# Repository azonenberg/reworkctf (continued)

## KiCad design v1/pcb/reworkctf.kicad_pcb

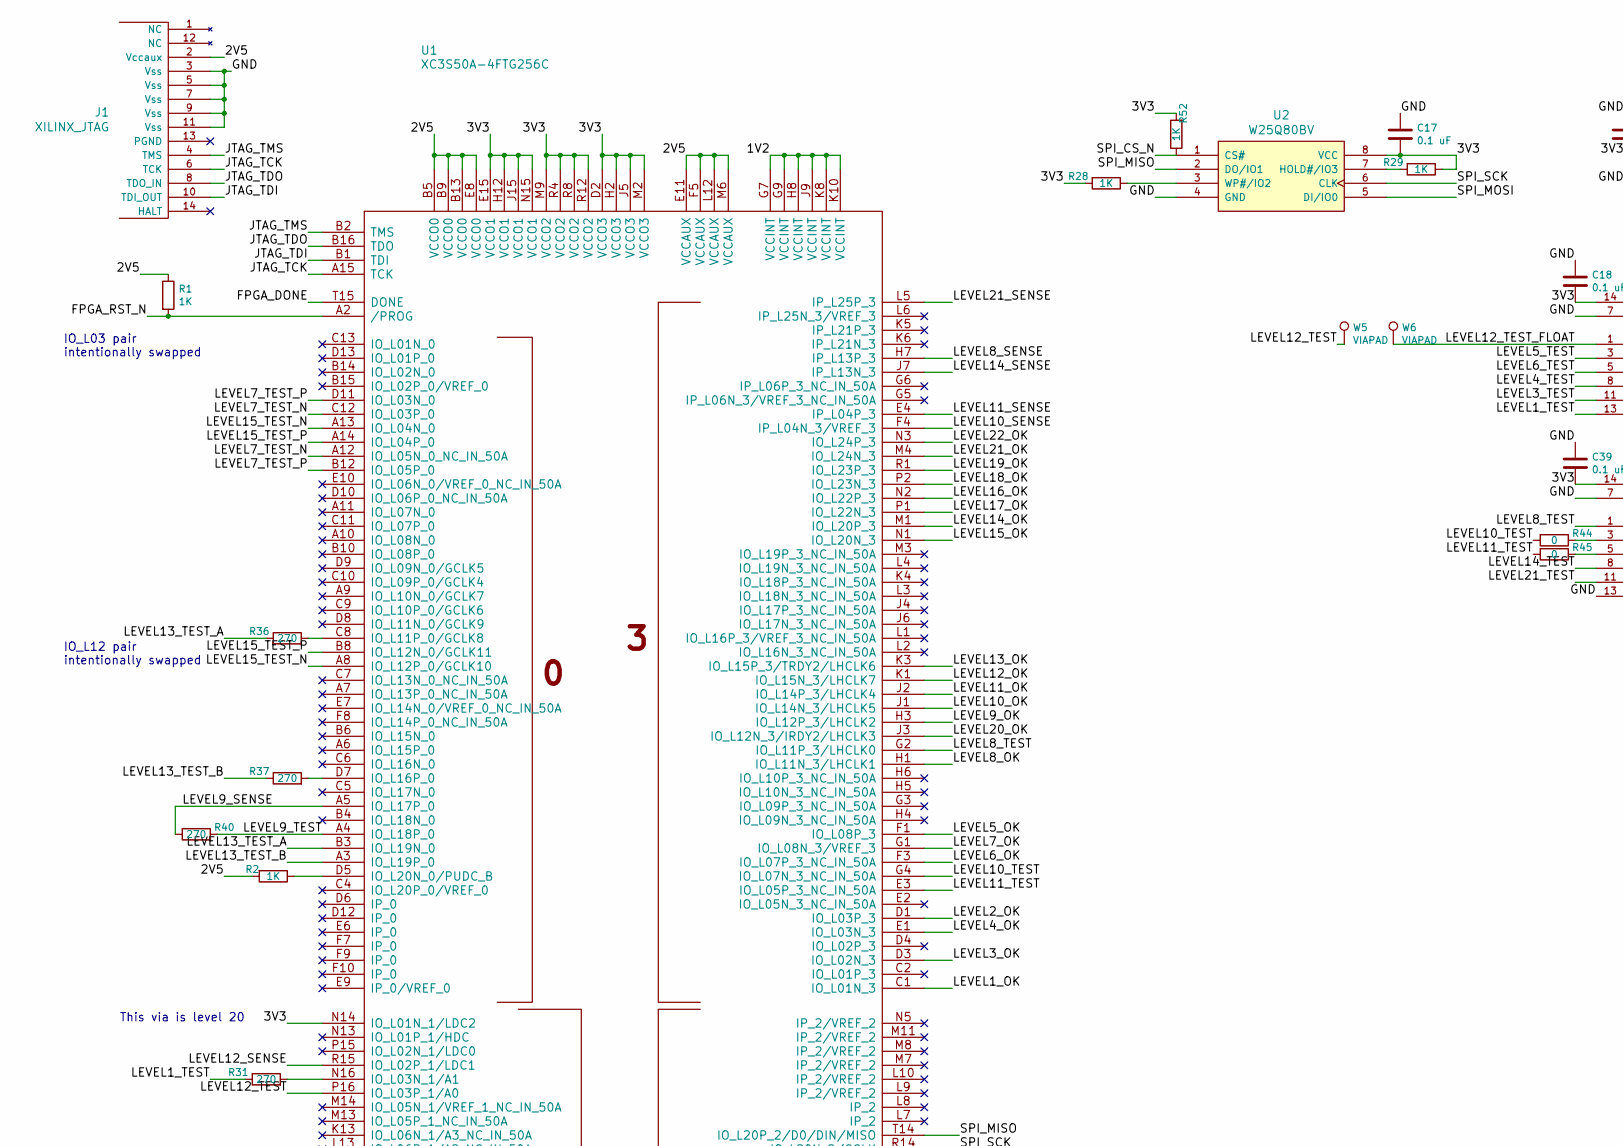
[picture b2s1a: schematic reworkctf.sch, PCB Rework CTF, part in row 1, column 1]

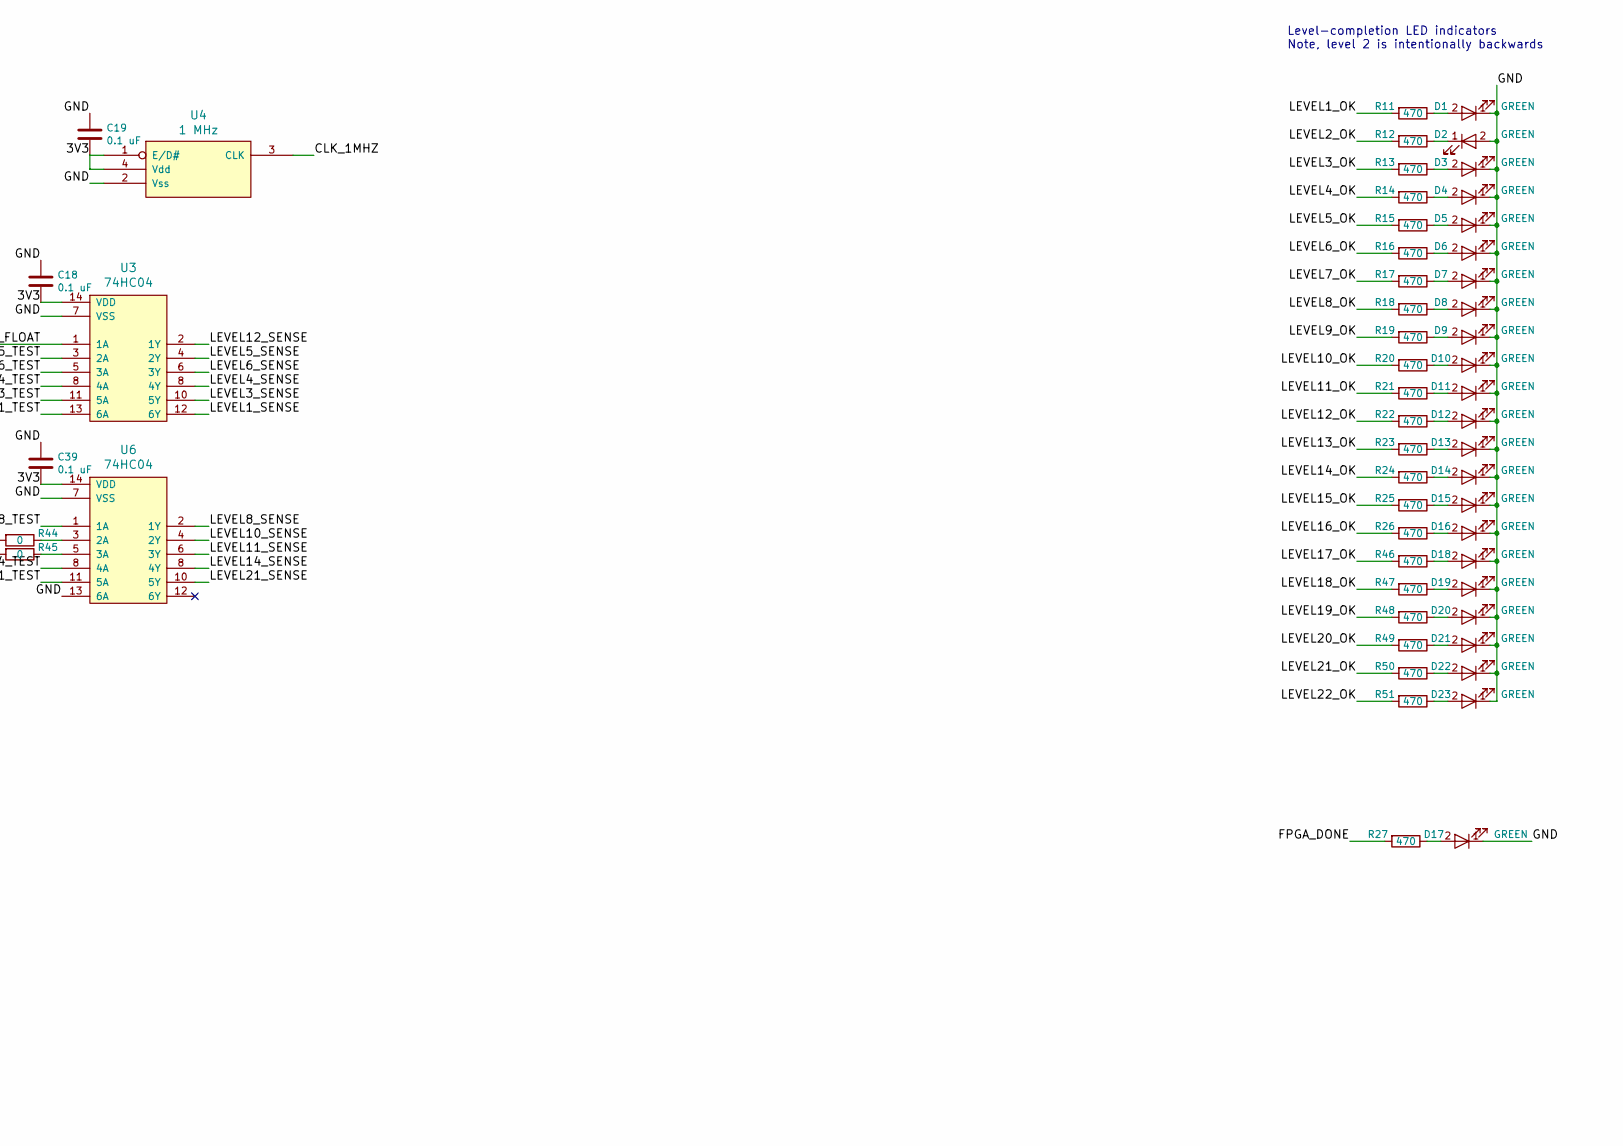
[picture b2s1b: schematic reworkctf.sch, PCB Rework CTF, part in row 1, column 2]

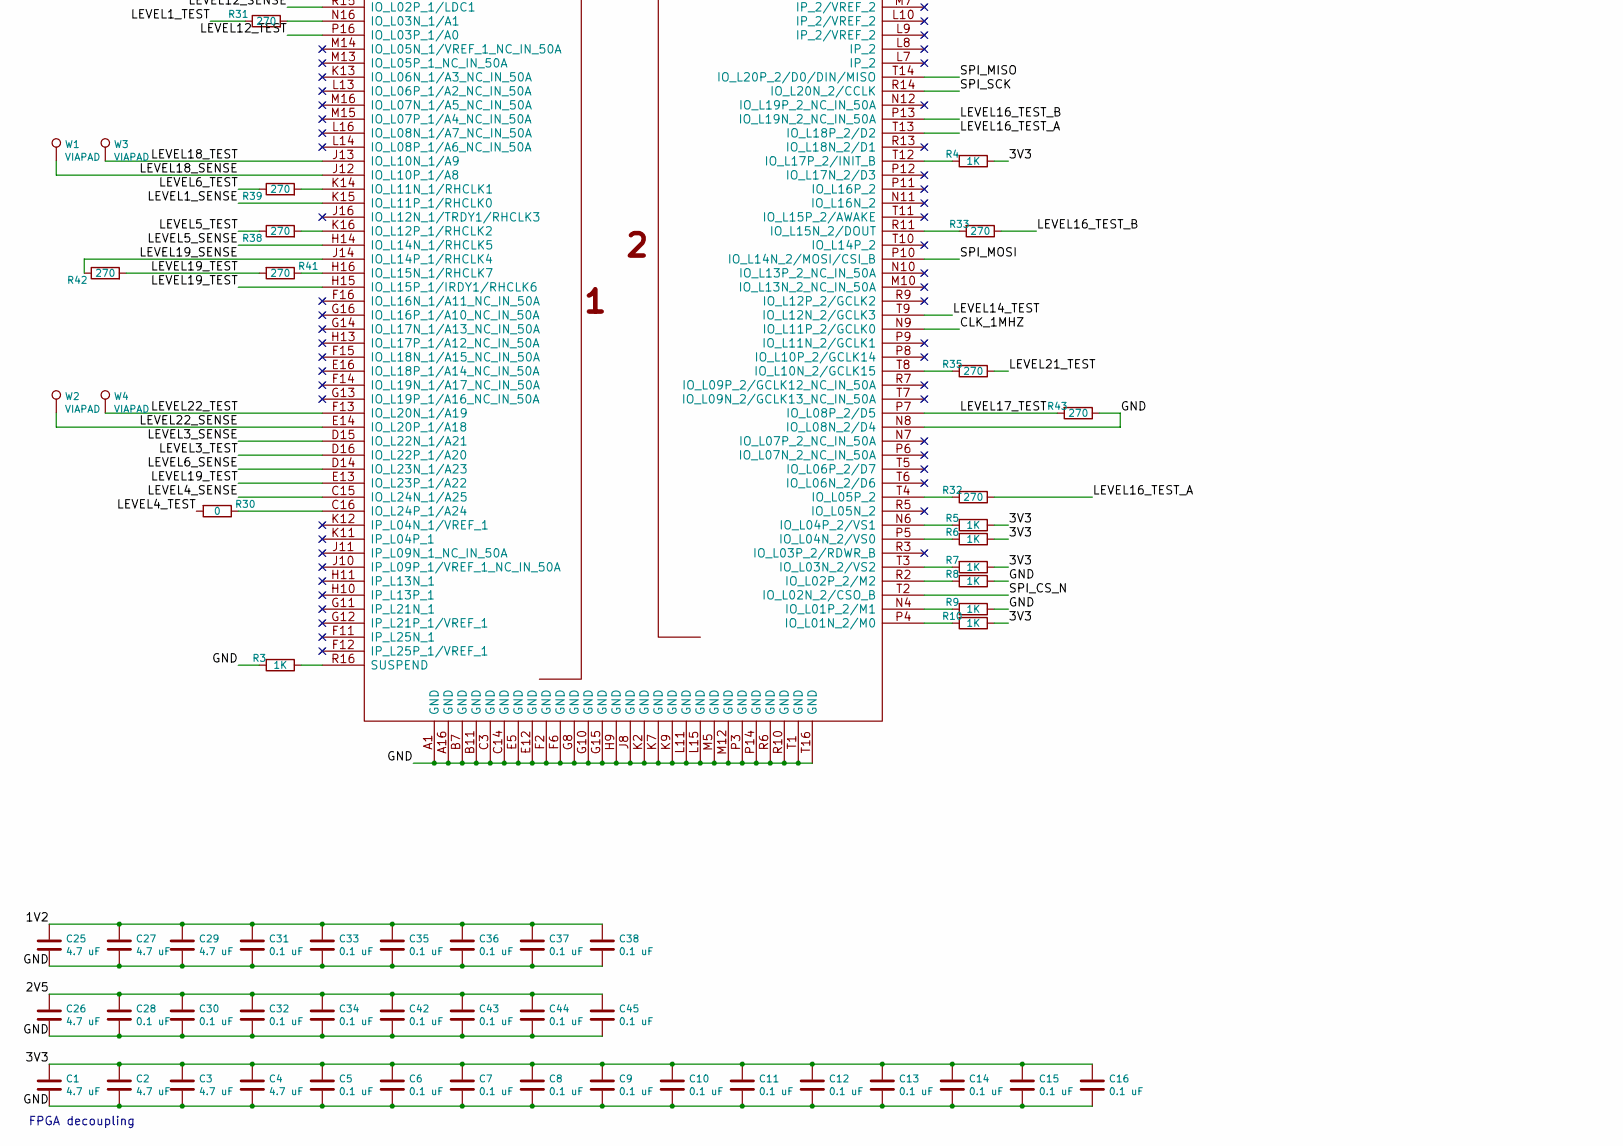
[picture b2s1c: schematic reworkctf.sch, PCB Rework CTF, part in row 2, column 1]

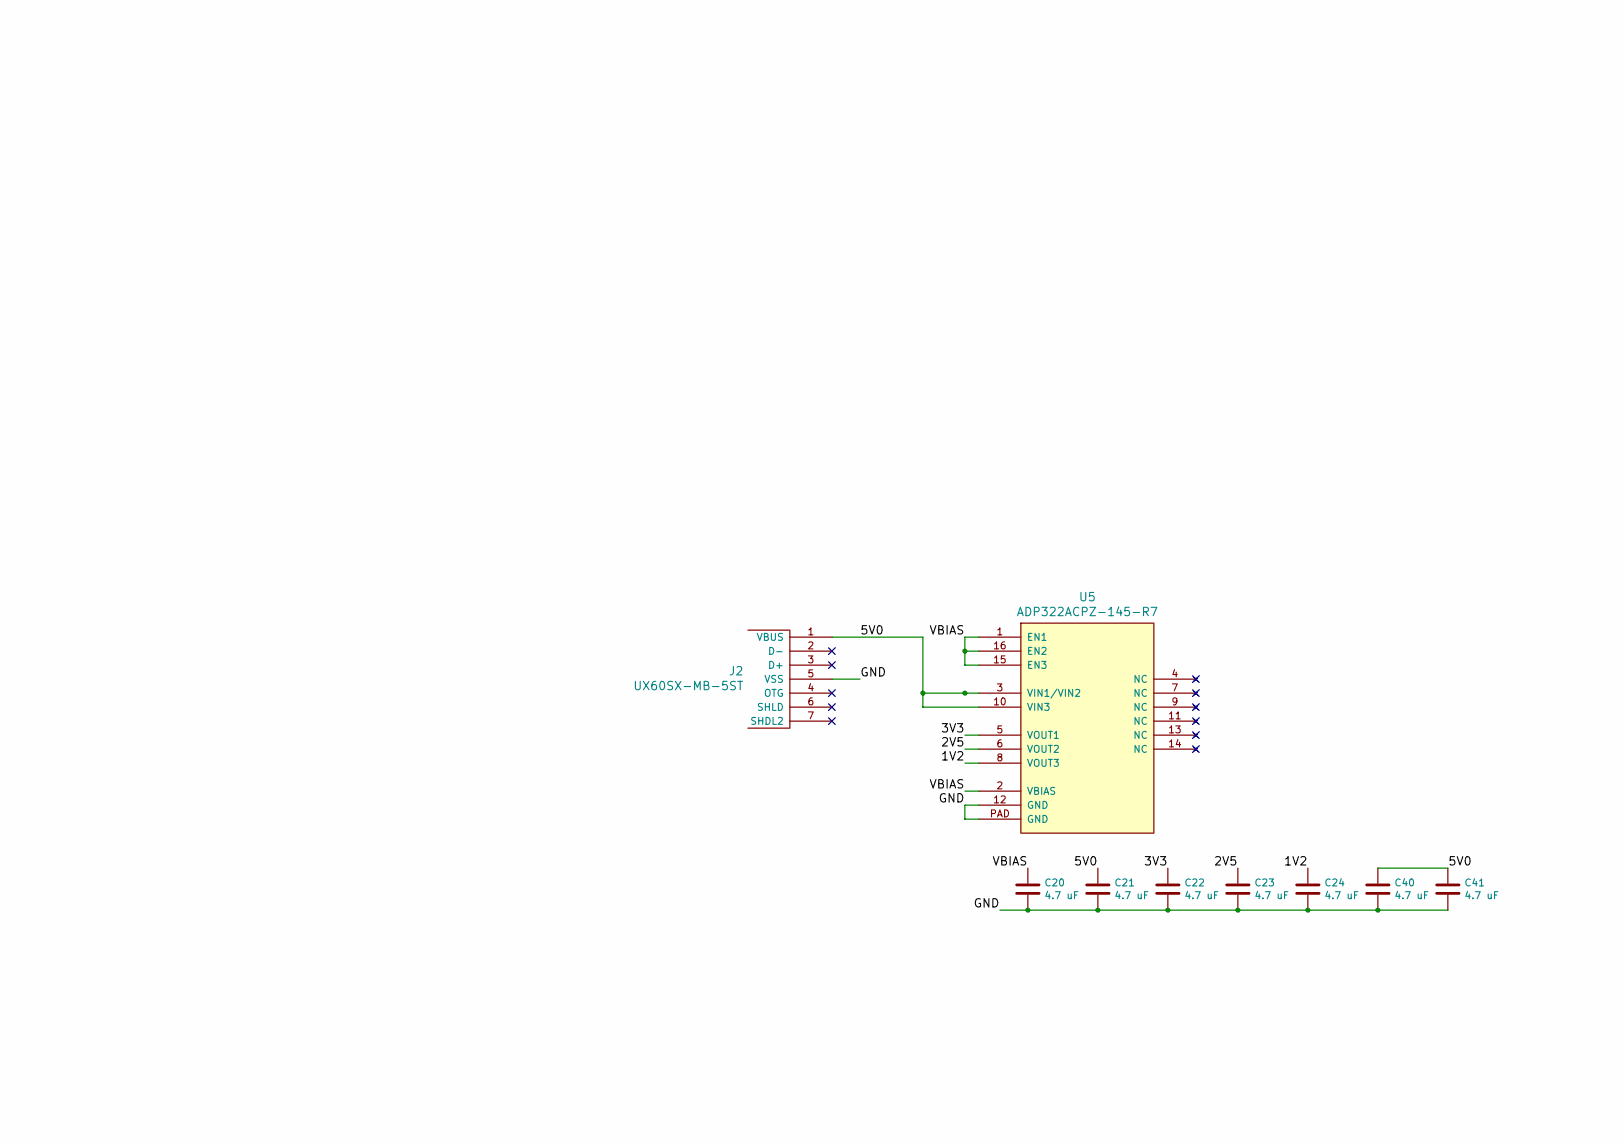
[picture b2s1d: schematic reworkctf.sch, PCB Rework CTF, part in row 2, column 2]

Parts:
C1, C2, C3, C4, C20, C21, C22, C23, C24, C25, C26, C27, C29, C40, C41: 4.7 uF; EIA_0603_CAP_NOSILK
C5, C6, C7, C8, C9, C10, C11, C12, C13, C14, C15, C16, C17, C18, C19, C28, C30, C31, C32, C33, C34, C35, C36, C37, C38, C39, C42, C43, C44, C45: 0.1 uF; EIA_0402_CAP_NOSILK
D1, D2, D3, D4, D5, D6, D7, D8, D9, D10, D11, D12, D13, D14, D15, D16, D17, D18, D19, D20, D21, D22, D23: GREEN; EIA_0603_LED
J1: XILINX_JTAG; XILINX_JTAG_PTH_MOLEX_0878311420
J2: UX60SX-MB-5ST; CONN_HIROSE_UX60S-MB-5ST_MINI_USB
R1, R2, R3, R4, R5, R6, R7, R8, R9, R10, R28, R29, R52: 1K; EIA_0402_RES_NOSILK
R11, R12, R13, R14, R15, R16, R17, R18, R19, R20, R21, R22, R23, R24, R25, R26, R27, R46, R47, R48, R49, R50, R51: 470; EIA_0402_RES_NOSILK
R30: 0; EIA_0805_CAP_NOSILK
R31, R32, R33, R35, R36, R37, R38, R39, R41, R42, R43: 270; EIA_0402_RES_NOSILK
R40: 270; EIA_01005_RES_NOSILK
R44: 0; EIA_0402_RES_NOSILK
R45: 0; EIA_0201_RES_NOSILK
U1: XC3S50A-4FTG256C; BGA_256_17x17_FULLARRAY_1MM
U2: W25Q80BV; SOIC_8_3.9MM
U3: 74HC04; SOIC_14_3.9MM_NOPIN11
U4: 1 MHz; OSCILLATOR_3.2x2.5
U5: ADP322ACPZ-145-R7; QFN_16_0.5MM_3x3MM
U6: 74HC04; TSSOP_14_0.65MM_5p6MM_NOPINS_1_2
W1, W2, W3, W4, W5, W6: VIAPAD; TESTPOINT_SMT_0.5MM

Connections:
/1V2: C24.1, C25.1, C27.1, C29.1, C31.1, C33.1, C35.1, C36.1, C37.1, C38.1, U1.G7 (VCCINT), U1.G9 (VCCINT), U1.H8 (VCCINT), U1.J9 (VCCINT), U1.K8 (VCCINT), U1.K10 (VCCINT), U5.8 (VOUT3)
/2V5: C23.1, C26.1, C28.1, C30.1, C32.1, C34.1, C42.1, C43.1, C44.1, C45.1, J1.2 (Vccaux), R1.1, R2.2, U1.B5 (VCCO0), U1.B9 (VCCO0), U1.B13 (VCCO0), U1.E8 (VCCO0), U1.E11 (VCCAUX), U1.F5 (VCCAUX), U1.L12 (VCCAUX), U1.M6 (VCCAUX), U5.6 (VOUT2)
/3V3: C1.1, C2.1, C3.1, C4.1, C5.1, C6.1, C7.1, C8.1, C9.1, C10.1, C11.1, C12.1, C13.1, C14.1, C15.1, C16.1, C17.2, C18.2, C19.2, C22.1, C39.2, R4.1, R5.1, R6.1, R7.1, R10.1, R28.2, R29.1, R52.2, U1.D2 (VCCO3), U1.E15 (VCCO1), U1.H2 (VCCO3), U1.H12 (VCCO1), U1.J5 (VCCO3), U1.J15 (VCCO1), U1.M2 (VCCO3), U1.M9 (VCCO2), U1.N14 (IO_L01N_1/LDC2), U1.N15 (VCCO1), U1.R4 (VCCO2), U1.R8 (VCCO2), U1.R12 (VCCO2), U2.8 (VCC), U3.14 (VDD), U4.1 (E/D#), U4.4 (Vdd), U5.5 (VOUT1), U6.14 (VDD)
/5V0: C21.1, C40.1, C41.1, J2.1 (VBUS), U5.3 (VIN1/VIN2), U5.10 (VIN3)
/CLK_1MHZ: U1.N9 (IO_L11P_2/GCLK0), U4.3 (CLK)
/FPGA_DONE: R27.2, U1.T15 (DONE)
/FPGA_RST_N: R1.2, U1.A2 (/PROG)
/GND: C1.2, C2.2, C3.2, C4.2, C5.2, C6.2, C7.2, C8.2, C9.2, C10.2, C11.2, C12.2, C13.2, C14.2, C15.2, C16.2, C17.1, C18.1, C19.1, C20.2, C21.2, C22.2, C23.2, C24.2, C25.2, C26.2, C27.2, C28.2, C29.2, C30.2, C31.2, C32.2, C33.2, C34.2, C35.2, C36.2, C37.2, C38.2, C39.1, C40.2, C41.2, C42.2, C43.2, C44.2, C45.2, D1.1 (K), D2.2 (A), D3.1 (K), D4.1 (K), D5.1 (K), D6.1 (K), D7.1 (K), D8.1 (K), D9.1 (K), D10.1 (K), D11.1 (K), D12.1 (K), D13.1 (K), D14.1 (K), D15.1 (K), D16.1 (K), D17.1 (K), D18.1 (K), D19.1 (K), D20.1 (K), D21.1 (K), D22.1 (K), D23.1 (K), J1.3 (Vss), J1.5 (Vss), J1.7 (Vss), J1.9 (Vss), J1.11 (Vss), J2.5 (VSS), R3.2, R8.1, R9.1, R43.1, U1.A1 (GND), U1.A16 (GND), U1.B7 (GND), U1.B11 (GND), U1.C3 (GND), U1.C14 (GND), U1.E5 (GND), U1.E12 (GND), U1.F2 (GND), U1.F6 (GND), U1.G8 (GND), U1.G10 (GND), U1.G15 (GND), U1.H9 (GND), U1.J8 (GND), U1.K2 (GND), U1.K7 (GND), U1.K9 (GND), U1.L11 (GND), U1.L15 (GND), U1.M5 (GND), U1.M12 (GND), U1.N8 (IO_L08N_2/D4), U1.P3 (GND), U1.P14 (GND), U1.R6 (GND), U1.R10 (GND), U1.T1 (GND), U1.T16 (GND), U2.4 (GND), U3.7 (VSS), U4.2 (Vss), U5.12 (GND), U5.PAD (GND), U6.7 (VSS), U6.13 (6A)
/JTAG_TCK: J1.6 (TCK), U1.A15 (TCK)
/JTAG_TDI: J1.10 (TDI_OUT), U1.B1 (TDI)
/JTAG_TDO: J1.8 (TDO_IN), U1.B16 (TDO)
/JTAG_TMS: J1.4 (TMS), U1.B2 (TMS)
/LEVEL1_OK: R11.2, U1.C1 (IO_L01N_3)
/LEVEL1_SENSE: U1.K15 (IO_L11P_1/RHCLK0), U3.12 (6Y)
/LEVEL1_TEST: R31.1, U3.13 (6A)
/LEVEL2_OK: R12.2, U1.D1 (IO_L03P_3)
/LEVEL3_OK: R13.2, U1.D3 (IO_L02N_3)
/LEVEL3_SENSE: U1.D15 (IO_L22N_1/A21), U3.10 (5Y)
/LEVEL3_TEST: U1.D16 (IO_L22P_1/A20), U3.11 (5A)
/LEVEL4_OK: R14.2, U1.E1 (IO_L03N_3)
/LEVEL5_OK: R15.2, U1.F1 (IO_L08P_3)
/LEVEL5_SENSE: U1.H14 (IO_L14N_1/RHCLK5), U3.4 (2Y)
/LEVEL5_TEST: R38.1, U3.3 (2A)
/LEVEL6_OK: R16.2, U1.F3 (IO_L07P_3_NC_IN_50A)
/LEVEL6_SENSE: U1.D14 (IO_L23N_1/A23), U3.6 (3Y)
/LEVEL6_TEST: R39.1, U3.5 (3A)
/LEVEL7_OK: R17.2, U1.G1 (IO_L08N_3/VREF_3)
/LEVEL7_TEST_N: U1.A12 (IO_L05N_0_NC_IN_50A), U1.C12 (IO_L03P_0)
/LEVEL7_TEST_P: U1.B12 (IO_L05P_0), U1.D11 (IO_L03N_0)
/LEVEL8_OK: R18.2, U1.H1 (IO_L11N_3/LHCLK1)
/LEVEL8_SENSE: U1.H7 (IP_L13P_3), U6.2 (1Y)
/LEVEL8_TEST: U1.G2 (IO_L11P_3/LHCLK0), U6.1 (1A)
/LEVEL9_OK: R19.2, U1.H3 (IO_L12P_3/LHCLK2)
/LEVEL9_SENSE: R40.2, U1.A5 (IO_L17P_0)
/LEVEL9_TEST: R40.1, U1.A4 (IO_L18P_0)
/LEVEL10_OK: R20.2, U1.J1 (IO_L14N_3/LHCLK5)
/LEVEL10_SENSE: U1.F4 (IP_L04N_3/VREF_3), U6.4 (2Y)
/LEVEL10_TEST: R44.2, U1.G4 (IO_L07N_3_NC_IN_50A)
/LEVEL11_OK: R21.2, U1.J2 (IO_L14P_3/LHCLK4)
/LEVEL11_SENSE: U1.E4 (IP_L04P_3), U6.6 (3Y)
/LEVEL11_TEST: R45.2, U1.E3 (IO_L05P_3_NC_IN_50A)
/LEVEL12_OK: R22.2, U1.K1 (IO_L15N_3/LHCLK7)
/LEVEL12_SENSE: U1.R15 (IO_L02P_1/LDC1), U3.2 (1Y)
/LEVEL12_TEST: U1.P16 (IO_L03P_1/A0), W5.1
/LEVEL12_TEST_FLOAT: U3.1 (1A), W6.1
/LEVEL13_OK: R23.2, U1.K3 (IO_L15P_3/TRDY2/LHCLK6)
/LEVEL13_TEST_A: R36.1, U1.B3 (IO_L19N_0)
/LEVEL13_TEST_B: R37.1, U1.A3 (IO_L19P_0)
/LEVEL14_OK: R24.2, U1.M1 (IO_L20P_3)
/LEVEL15_OK: R25.2, U1.N1 (IO_L20N_3)
/LEVEL15_TEST_N: U1.A8 (IO_L12P_0/GCLK10), U1.A13 (IO_L04N_0)
/LEVEL15_TEST_P: U1.A14 (IO_L04P_0), U1.B8 (IO_L12N_0/GCLK11)
/LEVEL16_OK: R26.2, U1.N2 (IO_L22P_3)
/LEVEL16_TEST_A: R32.1, U1.T13 (IO_L18P_2/D2)
/LEVEL16_TEST_B: R33.1, U1.P13 (IO_L19N_2_NC_IN_50A)
/LEVEL17_OK: R46.2, U1.P1 (IO_L22N_3)
/LEVEL17_TEST: R43.2, U1.P7 (IO_L08P_2/D5)
/LEVEL18_OK: R47.2, U1.P2 (IO_L23N_3)
/LEVEL18_SENSE: U1.J12 (IO_L10P_1/A8), W1.1
/LEVEL18_TEST: U1.J13 (IO_L10N_1/A9), W3.1
/LEVEL19_OK: R48.2, U1.R1 (IO_L23P_3)
/LEVEL19_SENSE: R42.1, U1.J14 (IO_L14P_1/RHCLK4)
/LEVEL19_TEST: R41.2, R42.2, U1.E13 (IO_L23P_1/A22), U1.H15 (IO_L15P_1/IRDY1/RHCLK6)
/LEVEL20_OK: R49.2, U1.J3 (IO_L12N_3/IRDY2/LHCLK3)
/LEVEL21_OK: R50.2, U1.M4 (IO_L24N_3)
/LEVEL21_SENSE: U1.L5 (IP_L25P_3), U6.10 (5Y)
/LEVEL21_TEST: R35.1, U6.11 (5A)
/LEVEL22_OK: R51.2, U1.N3 (IO_L24P_3)
/LEVEL22_SENSE: U1.E14 (IO_L20P_1/A18), W2.1
/LEVEL22_TEST: U1.F13 (IO_L20N_1/A19), W4.1
/SPI_CS_N: R52.1, U1.T2 (IO_L02N_2/CSO_B), U2.1 (CS#)
/SPI_MISO: U1.T14 (IO_L20P_2/D0/DIN/MISO), U2.2 (DO/IO1)
/SPI_MOSI: U1.P10 (IO_L14N_2/MOSI/CSI_B), U2.5 (DI/IO0)
/SPI_SCK: U1.R14 (IO_L20N_2/CCLK), U2.6 (CLK)
/VBIAS: C20.1, U5.1 (EN1), U5.2 (VBIAS), U5.15 (EN3), U5.16 (EN2)
unnamed: D1.2 (A), R11.1
unnamed: D2.1 (K), R12.1
unnamed: D3.2 (A), R13.1
unnamed: D4.2 (A), R14.1
unnamed: D5.2 (A), R15.1
unnamed: D6.2 (A), R16.1
unnamed: D7.2 (A), R17.1
unnamed: D8.2 (A), R18.1
unnamed: D9.2 (A), R19.1
unnamed: D10.2 (A), R20.1
unnamed: D11.2 (A), R21.1
unnamed: D12.2 (A), R22.1
unnamed: D13.2 (A), R23.1
unnamed: D14.2 (A), R24.1
unnamed: D15.2 (A), R25.1
unnamed: D16.2 (A), R26.1
unnamed: D17.2 (A), R27.1
unnamed: D18.2 (A), R46.1
unnamed: D19.2 (A), R47.1
unnamed: D20.2 (A), R48.1
unnamed: D21.2 (A), R49.1
unnamed: D22.2 (A), R50.1
unnamed: D23.2 (A), R51.1
unnamed: R2.1, U1.D5 (IO_L20N_0/PUDC_B)
unnamed: R3.1, U1.R16 (SUSPEND)
unnamed: R4.2, U1.T12 (IO_L17P_2/INIT_B)
unnamed: R5.2, U1.N6 (IO_L04P_2/VS1)
unnamed: R6.2, U1.P5 (IO_L04N_2/VS0)
unnamed: R7.2, U1.T3 (IO_L03N_2/VS2)
unnamed: R8.2, U1.R2 (IO_L02P_2/M2)
unnamed: R9.2, U1.N4 (IO_L01P_2/M1)
unnamed: R10.2, U1.P4 (IO_L01N_2/M0)
unnamed: R28.1, U2.3 (WP#/IO2)
unnamed: R29.2, U2.7 (HOLD#/IO3)
unnamed: R30.1, U1.C16 (IO_L24P_1/A24)
unnamed: R31.2, U1.N16 (IO_L03N_1/A1)
unnamed: R32.2, U1.T4 (IO_L05P_2)
unnamed: R33.2, U1.R11 (IO_L15N_2/DOUT)
unnamed: R35.2, U1.T8 (IO_L10N_2/GCLK15)
unnamed: R36.2, U1.C8 (IO_L11P_0/GCLK8)
unnamed: R37.2, U1.D7 (IO_L16P_0)
unnamed: R38.2, U1.K16 (IO_L12P_1/RHCLK2)
unnamed: R39.2, U1.K14 (IO_L11N_1/RHCLK1)
unnamed: R41.1, U1.H16 (IO_L15N_1/RHCLK7)
unnamed: R44.1, U6.3 (2A)
unnamed: R45.1, U6.5 (3A)

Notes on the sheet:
Level-completion LED indicators Note, level 2 is intentionally backwards
IO_L03 pair intentionally swapped
FPGA decoupling
IO_L12 pair intentionally swapped
This via is level 20

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
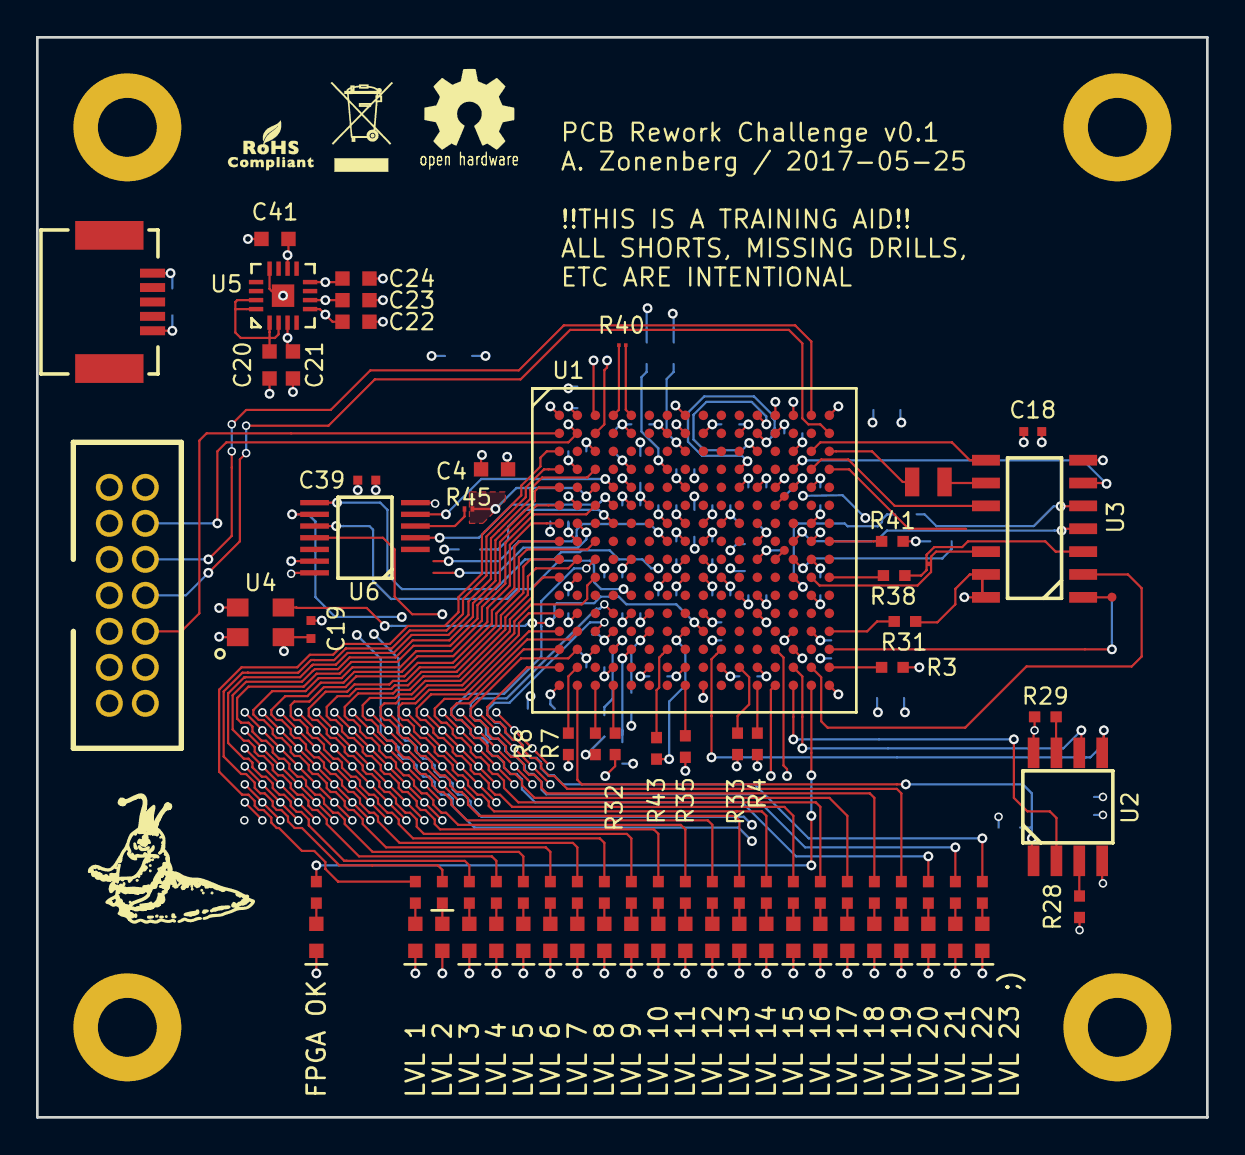
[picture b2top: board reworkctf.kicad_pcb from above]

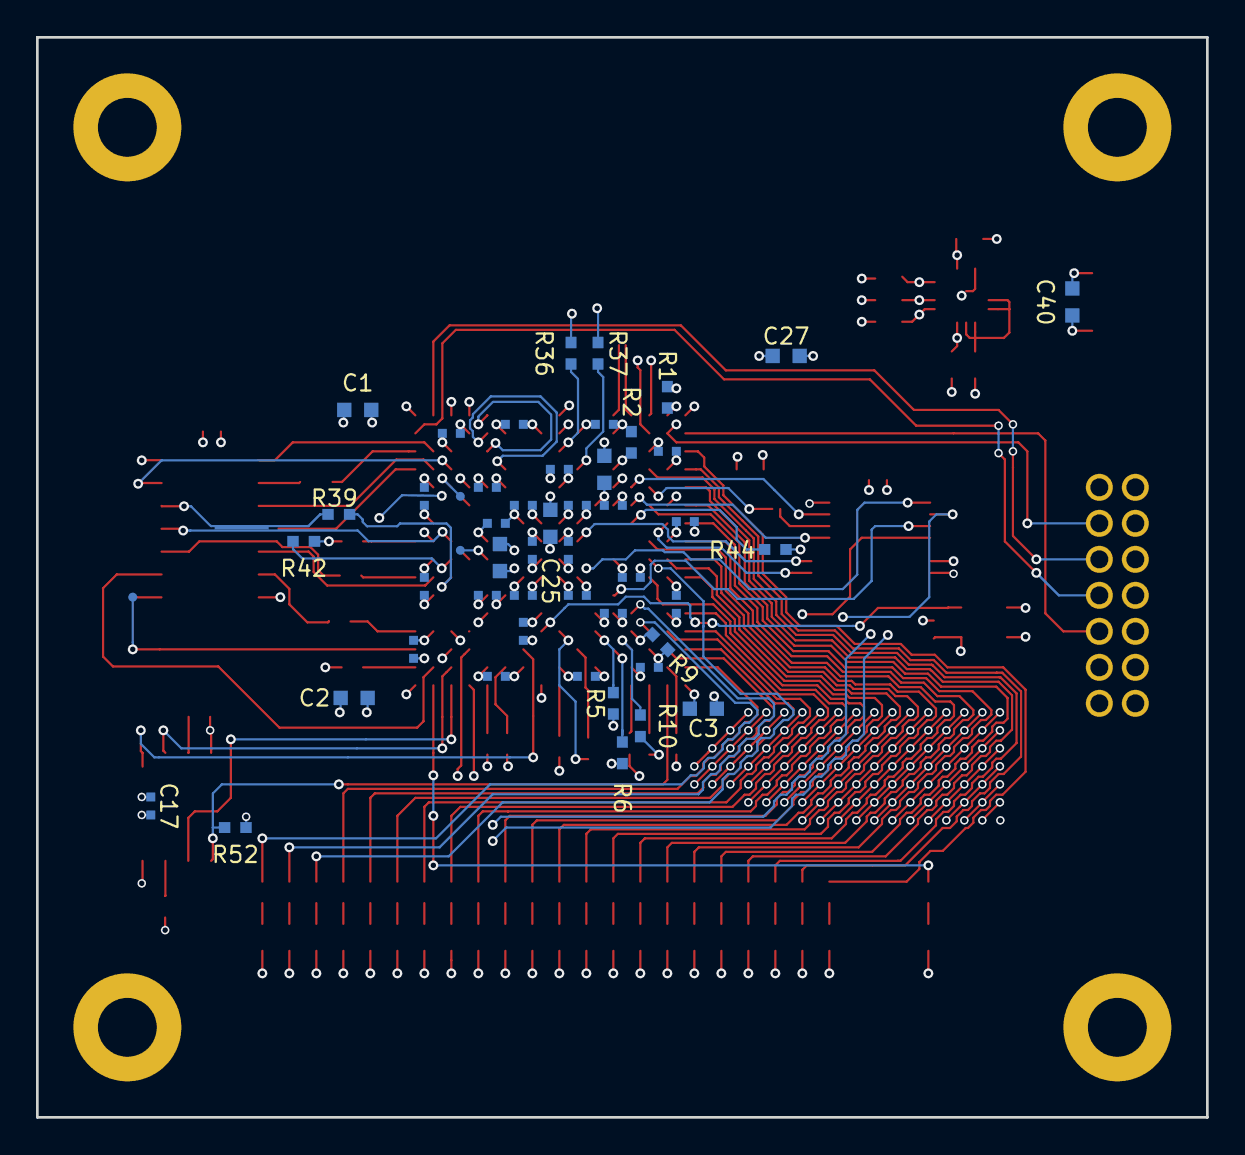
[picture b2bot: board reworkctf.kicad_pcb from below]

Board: 4 copper layers, 65.0 x 60.0 mm, 136 parts (51 on the bottom side), 125 nets.

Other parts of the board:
LEVEL2_SHORT, LEVEL5_SHORT, LEVEL6_SHORT: TESTPOINT_BARETRACE_150UM

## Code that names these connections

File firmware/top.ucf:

NET "level1_test" LOC = N16;
NET "level1_test" IOSTANDARD = LVCMOS33;
NET "level1_sense" LOC = K15;
NET "level1_sense" IOSTANDARD = LVCMOS33;
NET "level1_sense" PULLDOWN;

NET "level3_sense" LOC = D15;
NET "level3_sense" IOSTANDARD = LVCMOS33;
NET "level3_sense" PULLDOWN;
NET "level3_test" LOC = D16;
NET "level3_test" IOSTANDARD = LVCMOS33;

NET "level4_sense" LOC = C15;
NET "level4_sense" IOSTANDARD = LVCMOS33;
NET "level4_sense" PULLDOWN;
NET "level4_test" LOC = C16;
NET "level4_test" IOSTANDARD = LVCMOS33;

NET "level5_test" LOC = K16;
NET "level5_test" IOSTANDARD = LVCMOS33;
NET "level5_sense" LOC = H14;
NET "level5_sense" IOSTANDARD = LVCMOS33;
NET "level5_sense" PULLDOWN;

NET "level6_test" LOC = K14;
NET "level6_test" IOSTANDARD = LVCMOS33;
NET "level6_sense" LOC = D14;
NET "level6_sense" IOSTANDARD = LVCMOS33;
NET "level6_sense" PULLDOWN;

NET "level7_sense_p" LOC = B12;
NET "level7_sense_p" IOSTANDARD = LVCMOS25;
NET "level7_test_p" LOC = C12;
NET "level7_test_p" IOSTANDARD = LVCMOS25;
NET "level7_test_n" LOC = D11;
NET "level7_test_n" IOSTANDARD = LVCMOS25;

NET "level8_sense" LOC = H7;
NET "level8_sense" IOSTANDARD = LVCMOS33;
NET "level8_test" LOC = G2;
NET "level8_test" IOSTANDARD = LVCMOS33;
NET "level8_sense" PULLDOWN;

NET "level9_sense" LOC = A5;
NET "level9_sense" IOSTANDARD = LVCMOS25;
NET "level9_test" LOC = A4;
NET "level9_test" IOSTANDARD = LVCMOS25;
NET "level9_sense" PULLDOWN;

NET "level10_sense" LOC = F4;
NET "level10_sense" IOSTANDARD = LVCMOS33;
NET "level10_sense" PULLDOWN;

NET "level11_sense" LOC = E4;
NET "level11_sense" IOSTANDARD = LVCMOS33;
NET "level11_sense" PULLDOWN;

NET "level12_sense" LOC = R15;
NET "level12_sense" IOSTANDARD = LVCMOS33;
NET "level12_test" LOC = P16;
NET "level12_test" IOSTANDARD = LVCMOS33;
NET "level12_sense" PULLDOWN;

NET "level13_test_a" LOC = C8;
NET "level13_test_a" IOSTANDARD = LVCMOS25;
NET "level13_test_b" LOC = D7;
NET "level13_test_b" IOSTANDARD = LVCMOS25;
NET "level13_sense_a" LOC = B3;
NET "level13_sense_a" IOSTANDARD = LVCMOS25;
NET "level13_sense_b" LOC = A3;
NET "level13_sense_b" IOSTANDARD = LVCMOS25;

NET "level14_sense" LOC = J7;
NET "level14_sense" IOSTANDARD = LVCMOS33;
NET "level14_test" LOC = T9;
NET "level14_test" IOSTANDARD = LVCMOS33;
NET "level14_sense" PULLDOWN;

NET "level15_test_n" LOC = A13;
NET "level15_test_p" LOC = A14;
NET "level15_sense_p" LOC = A8;
NET "level15_sense_p" IOSTANDARD = LVDS_25;
NET "level15_sense_n" LOC = B8;
NET "level15_sense_n" IOSTANDARD = LVDS_25;

NET "level16_sense_a" LOC = T13;
NET "level16_sense_a" IOSTANDARD = LVCMOS33;
NET "level16_test_b" LOC = R11;
NET "level16_test_b" IOSTANDARD = LVCMOS33;
NET "level16_test_a" LOC = T4;
NET "level16_test_a" IOSTANDARD = LVCMOS33;

NET "level17_test" LOC = P7;
NET "level17_test" IOSTANDARD = LVCMOS33;
NET "level17_sense" LOC = N8;
NET "level17_sense" IOSTANDARD = LVCMOS33;
NET "level17_sense" PULLDOWN;

NET "level18_test" LOC = J13;
NET "level18_test" IOSTANDARD = LVCMOS33;
NET "level18_sense" LOC = J12;
NET "level18_sense" IOSTANDARD = LVCMOS33;
NET "level18_sense" PULLDOWN;

NET "level19_sense_a" LOC = J14;
NET "level19_sense_a" IOSTANDARD = LVCMOS33;
NET "level19_test_a" LOC = E13;
NET "level19_test_a" IOSTANDARD = LVCMOS33;
NET "level19_test_b" LOC = H16;
NET "level19_test_b" IOSTANDARD = LVCMOS33;
NET "level19_sense_b" LOC = H15;
NET "level19_sense_b" IOSTANDARD = LVCMOS33;

NET "level20_sense" LOC = N14;
NET "level20_sense" IOSTANDARD = LVCMOS33;
NET "level20_sense" PULLUP;

NET "level21_sense" LOC = L5;
NET "level21_sense" IOSTANDARD = LVCMOS33;
NET "level21_test" LOC = T8 |IOSTANDARD = LVCMOS33;
NET "level21_test" IOSTANDARD = LVCMOS33;

NET "level22_sense" LOC = E14;
NET "level22_sense" IOSTANDARD = LVCMOS33;
NET "level22_test" LOC = F13;
NET "level22_test" IOSTANDARD = LVCMOS33;
NET "level22_sense" PULLDOWN;

NET "level_ok[0]" LOC = C1;
NET "level_ok[0]" IOSTANDARD = LVCMOS33;
NET "level_ok[1]" LOC = D1;
NET "level_ok[1]" IOSTANDARD = LVCMOS33;
NET "level_ok[2]" LOC = D3;
NET "level_ok[2]" IOSTANDARD = LVCMOS33;
NET "level_ok[3]" LOC = E1;
NET "level_ok[3]" IOSTANDARD = LVCMOS33;
NET "level_ok[4]" LOC = F1;
NET "level_ok[4]" IOSTANDARD = LVCMOS33;
# NOT the final location, but can rework this maybe?
NET "level_ok[5]" LOC = C2;
NET "level_ok[5]" IOSTANDARD = LVCMOS33;
NET "level_ok[6]" LOC = G1;
NET "level_ok[6]" IOSTANDARD = LVCMOS33;
NET "level_ok[7]" LOC = H1;
NET "level_ok[7]" IOSTANDARD = LVCMOS33;
NET "level_ok[8]" LOC = H3;
NET "level_ok[8]" IOSTANDARD = LVCMOS33;
NET "level_ok[9]" LOC = J1;
NET "level_ok[9]" IOSTANDARD = LVCMOS33;
NET "level_ok[10]" LOC = J2;
NET "level_ok[10]" IOSTANDARD = LVCMOS33;
NET "level_ok[11]" LOC = K1;
NET "level_ok[11]" IOSTANDARD = LVCMOS33;
NET "level_ok[12]" LOC = K3;
NET "level_ok[12]" IOSTANDARD = LVCMOS33;
NET "level_ok[13]" LOC = M1;
NET "level_ok[13]" IOSTANDARD = LVCMOS33;
NET "level_ok[14]" LOC = N1;
NET "level_ok[14]" IOSTANDARD = LVCMOS33;
NET "level_ok[15]" LOC = N2;
NET "level_ok[15]" IOSTANDARD = LVCMOS33;
NET "level_ok[16]" LOC = P1;
NET "level_ok[16]" IOSTANDARD = LVCMOS33;
NET "level_ok[17]" LOC = P2;
NET "level_ok[17]" IOSTANDARD = LVCMOS33;
NET "level_ok[18]" LOC = R1;
NET "level_ok[18]" IOSTANDARD = LVCMOS33;
NET "level_ok[19]" LOC = J3;
NET "level_ok[19]" IOSTANDARD = LVCMOS33;
NET "level_ok[20]" LOC = M4;
NET "level_ok[20]" IOSTANDARD = LVCMOS33;
NET "level_ok[21]" LOC = N3;
NET "level_ok[21]" IOSTANDARD = LVCMOS33;

NET "clk_1mhz" LOC = N9;
NET "clk_1mhz" IOSTANDARD = LVCMOS33;

NET "clk_1mhz" TNM_NET = "clk_1mhz";
TIMESPEC TS_clk_1mhz = PERIOD "clk_1mhz" 1 MHz HIGH 50 %;

# Use really weak drive strength to avoid capacitively coupling stuff
NET "level4_test" DRIVE = 2;

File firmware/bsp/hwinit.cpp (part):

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{
	//Initialize the UART for local console: 115.2 Kbps using PA9 for UART1 transmit and PA10 for UART1 receive
	//TODO: nice interface for enabling UART interrupts
	static GPIOPin uart_tx(&GPIOA, 9, GPIOPin::MODE_PERIPHERAL, GPIOPin::SLEW_SLOW, 7);
	static GPIOPin uart_rx(&GPIOA, 10, GPIOPin::MODE_PERIPHERAL, GPIOPin::SLEW_SLOW, 7);

	//Enable the UART interrupt
	NVIC_EnableIRQ(37);
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void GradeChallenge1()
{
	//Challenge 1: short between test signal and ground. Pull weakly high and see how it reads
	GPIOPin challenge_01(&GPIOA, 3, GPIOPin::MODE_INPUT, GPIOPin::SLEW_SLOW);
	challenge_01.SetPullMode(GPIOPin::PULL_UP);
	g_logTimer.Sleep(1);
	if(challenge_01)
	{
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void GradeChallenge4()
{
	//Just check for continuity through the resistor
	GPIOPin challenge_04(&GPIOJ, 3, GPIOPin::MODE_INPUT, GPIOPin::SLEW_SLOW);
	challenge_04.SetPullMode(GPIOPin::PULL_DOWN);
	g_logTimer.Sleep(1);

	if(!challenge_04)
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void GradeChallenge5()
{
	//Just check for continuity through the resistor
	GPIOPin challenge_05(&GPIOJ, 4, GPIOPin::MODE_INPUT, GPIOPin::SLEW_SLOW);
	challenge_05.SetPullMode(GPIOPin::PULL_DOWN);
	g_logTimer.Sleep(1);

	if(!challenge_05)
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void GradeChallenge8()
{
	//Just check for continuity through the break
	GPIOPin challenge_08_a(&GPIOG, 1, GPIOPin::MODE_OUTPUT, GPIOPin::SLEW_SLOW);
	GPIOPin challenge_08_b(&GPIOF, 11, GPIOPin::MODE_INPUT, GPIOPin::SLEW_SLOW);
	challenge_08_a = 1;
	challenge_08_b.SetPullMode(GPIOPin::PULL_DOWN);
	g_logTimer.Sleep(1);

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
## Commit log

2017-05-24 Finished initial work on reworkctf schematic and documentation
2017-05-24 Added extra-credit bug
2017-05-24 Initial work on layout
2017-05-24 Continued initial layout
2017-05-24 Continued work on initial layout
2017-05-24 Began work on active mesh
2017-05-26 Finished initial work on rework challenge board
2017-05-26 Removed soldermask openings on short circuits
2017-07-09 Initial version of grader firmware
2017-07-10 BUGFIX: level 9 should not be inverted
2026-03-16 Initial skeleton of v2 design
2026-03-17 Finished initial MCU layout, need to actually add challenges
2026-03-17 Got up to challenge 8
2026-03-17 Added challenge 7 with lifted pad on the soic
2026-03-17 Added note about challenge 6/7 challenge dependency
2026-03-17 Added challenge 9 with diffpair polarity swap on inner layer
2026-03-18 Added challenges 10 and 11 for vias
2026-03-18 Added SM-2 challenge, shrunk overall PCB footprint a bunch
2026-03-18 Added challenge 15 (missing pullup)
2026-03-18 Initial work on "free play area" sandbox
2026-03-18 Added more inner layer test features to free play area
2026-03-19 Added strap via to wrong net. Should be ready to order, I think
2026-03-19 Final version of v2 board including export settings
2026-03-19 Updated ignore properties
2026-04-02 Added a bunch of firmware submodules
2026-04-02 Initial firmware skeleton
2026-04-02 Began work on grader firmware
2026-04-02 Continued grader firmware
2026-04-02 Added more grader firmware
2026-04-03 Disable RTC in log messages since we have no time source
